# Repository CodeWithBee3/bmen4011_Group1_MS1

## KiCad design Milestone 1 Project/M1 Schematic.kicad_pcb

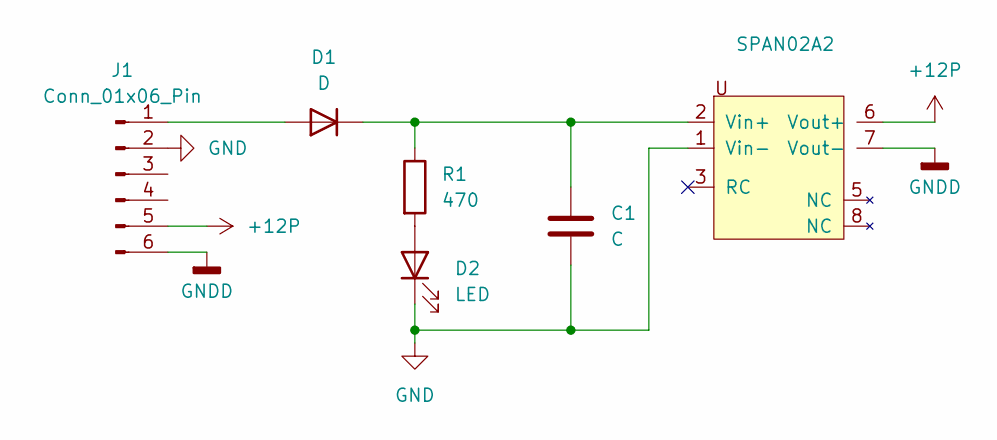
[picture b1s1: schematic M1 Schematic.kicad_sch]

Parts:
C1: C; C_0805_2012Metric
D1: D; D_SMA
D2: LED; LED_0805_2012Metric
J1: Conn_01x06_Pin; Molex_Micro-Fit_3.0_43045-0612_2x03_P3.00mm_Vertical
R1: 470; R_1206_3216Metric
SPAN02A2: SPAN02

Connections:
+12P: J1.5, SPAN02A2.6 (Vout+)
GND: C1.2, D2.1 (K), J1.2, SPAN02A2.1 (Vin-)
GNDD: J1.6, SPAN02A2.7 (Vout-)
unnamed: D1.2 (A), J1.1
unnamed: C1.1, D1.1 (K), R1.1, SPAN02A2.2 (Vin+)
unnamed: D2.2 (A), R1.2

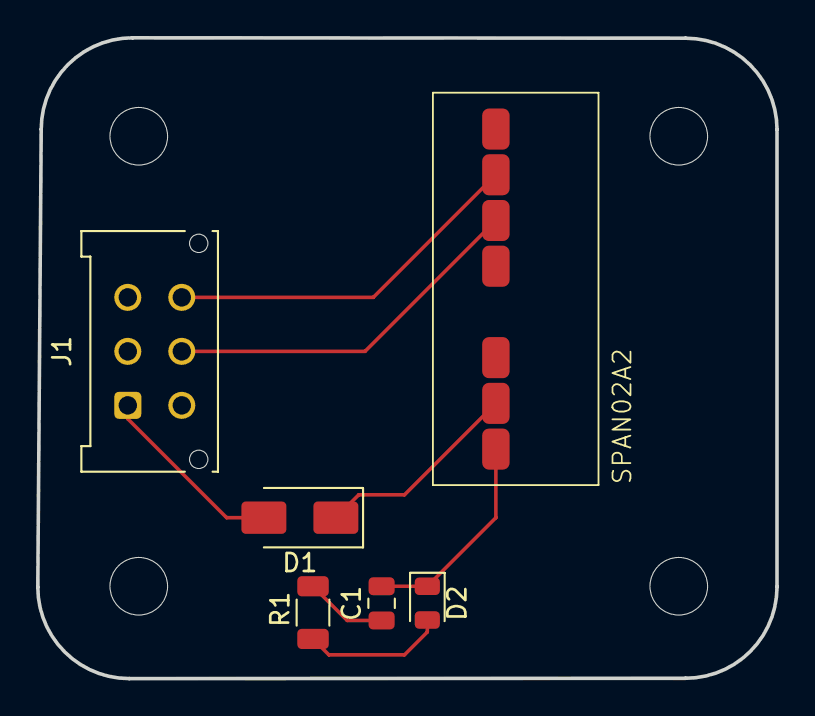
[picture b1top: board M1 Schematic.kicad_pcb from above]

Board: 2 copper layers, 41.1 x 35.6 mm, 6 parts (0 on the bottom side), 6 nets.

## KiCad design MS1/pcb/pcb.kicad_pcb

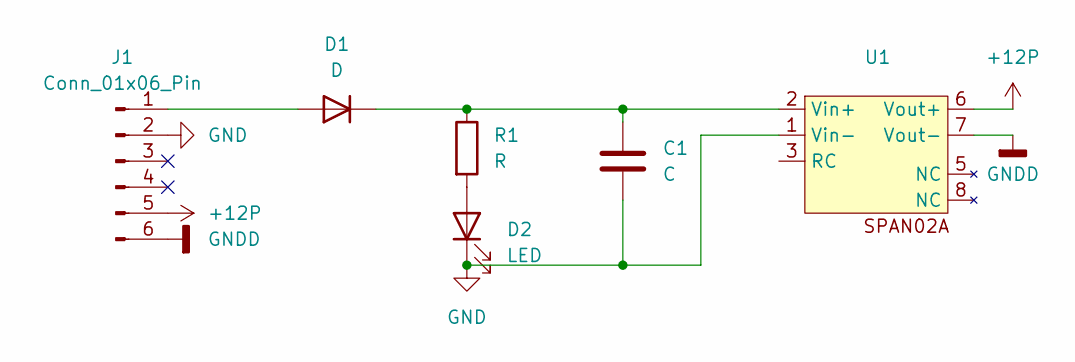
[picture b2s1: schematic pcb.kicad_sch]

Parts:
C1: C; C_0805_2012Metric
D1: D; D_SMA
D2: LED; LED_0805_2012Metric
J1: Conn_01x06_Pin; Molex_Micro-Fit_3.0_43045-0612_2x03_P3.00mm_Vertical
R1: R; R_1206_3216Metric
U1: SPAN02A

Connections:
+12P: J1.5, U1.6 (Vout+)
GND: C1.2, D2.1 (K), J1.2, U1.1 (Vin-)
GNDD: J1.6, U1.7 (Vout-)
unnamed: D1.2 (A), J1.1
unnamed: C1.1, D1.1 (K), R1.1, U1.2 (Vin+)
unnamed: D2.2 (A), R1.2

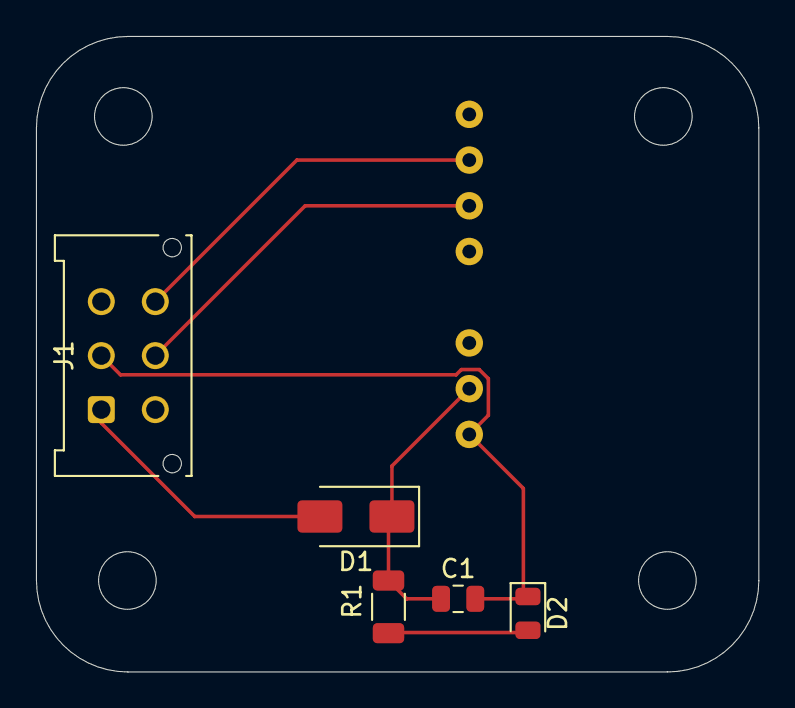
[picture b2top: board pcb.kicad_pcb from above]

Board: 2 copper layers, 40.1 x 35.3 mm, 6 parts (0 on the bottom side), 6 nets.

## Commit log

2024-09-29 Add files via upload
    plz work
